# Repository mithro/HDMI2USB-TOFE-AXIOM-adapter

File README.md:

# TOFE to AXIOM Adapter

This repository contains a board for adapting the
[TOFE interface](https://tofe.io/) to the interface used by the
[plugin modules for the AXIOM Beta](https://wiki.apertus.org/index.php/AXIOM_Beta/AXIOM_Beta_Hardware#Plugin_Modules).

These adapter boards are **transparent** to the TOFE bus and have identical
schematics, only the PCB design differs.

Any **passive** PCI-Express adapter or riser which meets the PCI-Express
specification should be also compatible with the TOFE interface (but the
reverse is not necessarily true).

For more information on;
 * [The TOFE interface, see the HDMI2USB website](http://hdmi2usb.tv/tofe).
 * [The AXIOM interface, see the AXIOM wiki](https://wiki.apertus.org/index.php/AXIOM_Beta)
 * KiCad software, see [KiCad website](http://kicad.org/).

## Editing

Download with
```
git clone git+ssh://git@github.com/mithro/HDMI2USB-TOFE-AXIOM-Adapter.git --recursive
```

The designs in this repository was made using [KiCad](http://www.kicad.org/)
version **4.0.2 BZR 6225**
([the current stable version of KiCad](http://kicad.org/download/)).

## License

This work is copyright TimVideos.us Developers 2015 and licensed under a
Creative Commons Attribution-ShareAlike 4.0 International License.

You should have received a copy of the license along with this
work.  If not, see <http://creativecommons.org/licenses/by-sa/4.0/>.

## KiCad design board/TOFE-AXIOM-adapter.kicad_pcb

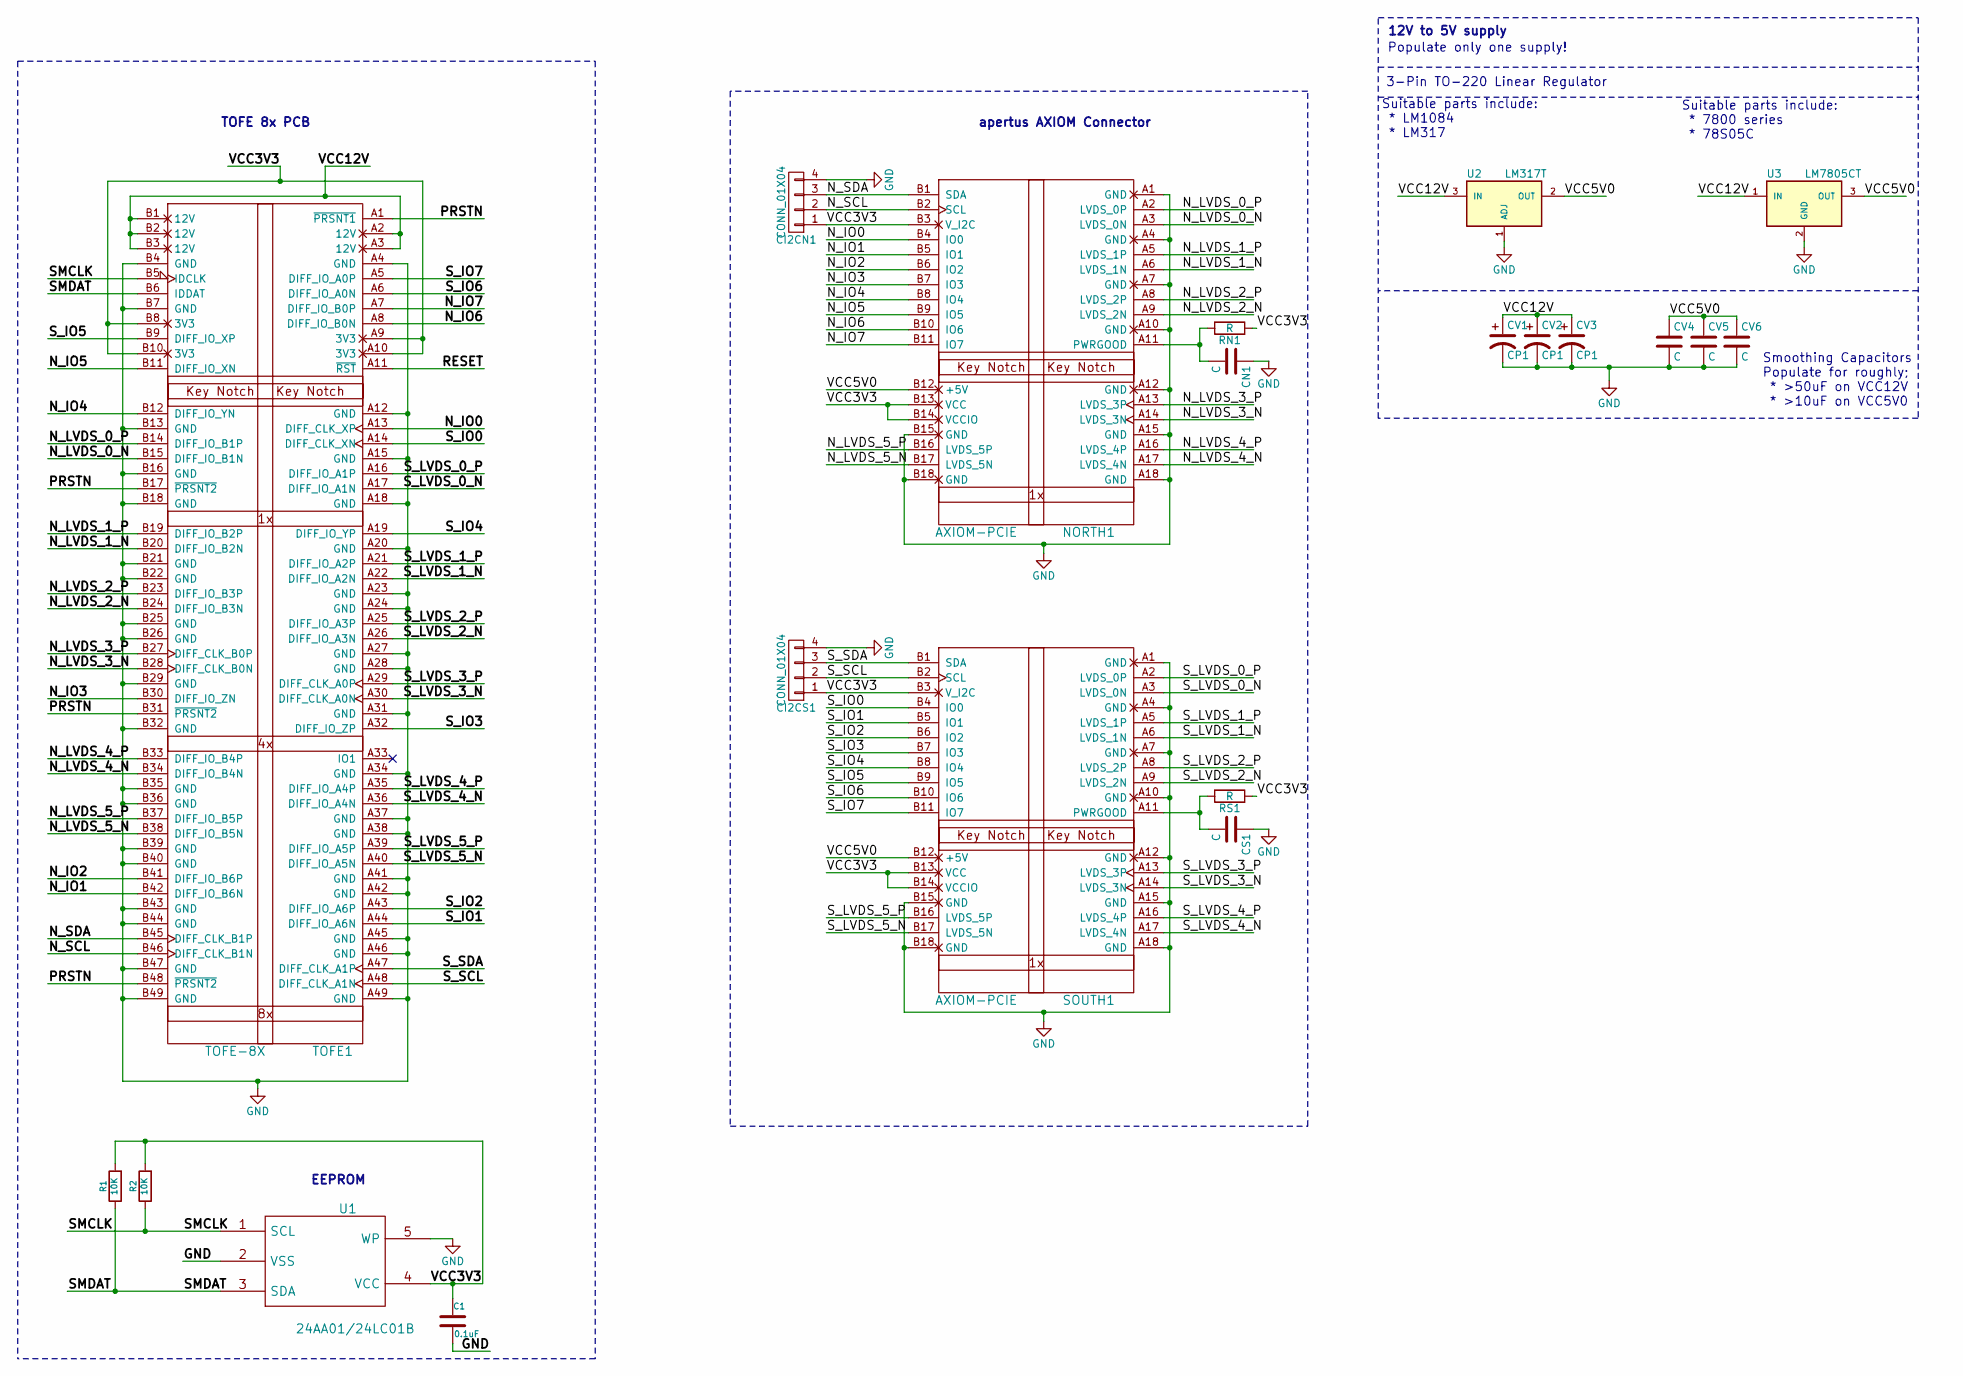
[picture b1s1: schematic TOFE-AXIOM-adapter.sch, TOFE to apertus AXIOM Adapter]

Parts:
C1: 0.1uF; C_1206_HandSoldering
CI2CN1, CI2CS1: CONN_01X04; Pin_Header_Straight_1x04
CN1: C; C_1206_HandSoldering
CS1: C; C_1206_HandSoldering
CV1, CV2, CV3: CP1; SMD-1206_Pol
CV4, CV5, CV6: C; C_1206_HandSoldering
NORTH1: AXIOM-PCIE; pci-x_conn-x1
R1, R2: 10K; R_0603_HandSoldering
RN1: R; R_0603_HandSoldering
RS1: R; R_0603_HandSoldering
SOUTH1: AXIOM-PCIE; pci-x_conn-x1
TOFE1: TOFE-8X; TOFE_8X_Pins
U1: 24AA01/24LC01B; SOT-23-5
U2: LM317T
U3: LM7805CT

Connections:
/N_IO0: NORTH1.B4 (IO0), TOFE1.A13 (DIFF_CLK_XP)
/N_IO1: NORTH1.B5 (IO1), TOFE1.B42 (DIFF_IO_B6N)
/N_IO2: NORTH1.B6 (IO2), TOFE1.B41 (DIFF_IO_B6P)
/N_IO3: NORTH1.B7 (IO3), TOFE1.B30 (DIFF_IO_ZN)
/N_IO4: NORTH1.B8 (IO4), TOFE1.B12 (DIFF_IO_YN)
/N_IO5: NORTH1.B9 (IO5), TOFE1.B11 (DIFF_IO_XN)
/N_IO6: NORTH1.B10 (IO6), TOFE1.A8 (DIFF_IO_B0N)
/N_IO7: NORTH1.B11 (IO7), TOFE1.A7 (DIFF_IO_B0P)
/N_LVDS_0_N: NORTH1.A3 (LVDS_0N), TOFE1.B15 (DIFF_IO_B1N)
/N_LVDS_0_P: NORTH1.A2 (LVDS_0P), TOFE1.B14 (DIFF_IO_B1P)
/N_LVDS_1_N: NORTH1.A6 (LVDS_1N), TOFE1.B20 (DIFF_IO_B2N)
/N_LVDS_1_P: NORTH1.A5 (LVDS_1P), TOFE1.B19 (DIFF_IO_B2P)
/N_LVDS_2_N: NORTH1.A9 (LVDS_2N), TOFE1.B24 (DIFF_IO_B3N)
/N_LVDS_2_P: NORTH1.A8 (LVDS_2P), TOFE1.B23 (DIFF_IO_B3P)
/N_LVDS_3_N: NORTH1.A14 (LVDS_3N), TOFE1.B28 (DIFF_CLK_B0N)
/N_LVDS_3_P: NORTH1.A13 (LVDS_3P), TOFE1.B27 (DIFF_CLK_B0P)
/N_LVDS_4_N: NORTH1.A17 (LVDS_4N), TOFE1.B34 (DIFF_IO_B4N)
/N_LVDS_4_P: NORTH1.A16 (LVDS_4P), TOFE1.B33 (DIFF_IO_B4P)
/N_LVDS_5_N: NORTH1.B17 (LVDS_5N), TOFE1.B38 (DIFF_IO_B5N)
/N_LVDS_5_P: NORTH1.B16 (LVDS_5P), TOFE1.B37 (DIFF_IO_B5P)
/N_SCL: CI2CN1.2, NORTH1.B2 (SCL), TOFE1.B46 (DIFF_CLK_B1N)
/N_SDA: CI2CN1.3, NORTH1.B1 (SDA), TOFE1.B45 (DIFF_CLK_B1P)
/PRSTN: TOFE1.A1 (~PRSNT1), TOFE1.B17 (~PRSNT2), TOFE1.B31 (~PRSNT2), TOFE1.B48 (~PRSNT2)
/RESET: TOFE1.A11 (~RST)
/SMCLK: R2.1, TOFE1.B5 (IDCLK), U1.1 (SCL)
/SMDAT: R1.1, TOFE1.B6 (IDDAT), U1.3 (SDA)
/S_IO0: SOUTH1.B4 (IO0), TOFE1.A14 (DIFF_CLK_XN)
/S_IO1: SOUTH1.B5 (IO1), TOFE1.A44 (DIFF_IO_A6N)
/S_IO2: SOUTH1.B6 (IO2), TOFE1.A43 (DIFF_IO_A6P)
/S_IO3: SOUTH1.B7 (IO3), TOFE1.A32 (DIFF_IO_ZP)
/S_IO4: SOUTH1.B8 (IO4), TOFE1.A19 (DIFF_IO_YP)
/S_IO5: SOUTH1.B9 (IO5), TOFE1.B9 (DIFF_IO_XP)
/S_IO6: SOUTH1.B10 (IO6), TOFE1.A6 (DIFF_IO_A0N)
/S_IO7: SOUTH1.B11 (IO7), TOFE1.A5 (DIFF_IO_A0P)
/S_LVDS_0_N: SOUTH1.A3 (LVDS_0N), TOFE1.A17 (DIFF_IO_A1N)
/S_LVDS_0_P: SOUTH1.A2 (LVDS_0P), TOFE1.A16 (DIFF_IO_A1P)
/S_LVDS_1_N: SOUTH1.A6 (LVDS_1N), TOFE1.A22 (DIFF_IO_A2N)
/S_LVDS_1_P: SOUTH1.A5 (LVDS_1P), TOFE1.A21 (DIFF_IO_A2P)
/S_LVDS_2_N: SOUTH1.A9 (LVDS_2N), TOFE1.A26 (DIFF_IO_A3N)
/S_LVDS_2_P: SOUTH1.A8 (LVDS_2P), TOFE1.A25 (DIFF_IO_A3P)
/S_LVDS_3_N: SOUTH1.A14 (LVDS_3N), TOFE1.A30 (DIFF_CLK_A0N)
/S_LVDS_3_P: SOUTH1.A13 (LVDS_3P), TOFE1.A29 (DIFF_CLK_A0P)
/S_LVDS_4_N: SOUTH1.A17 (LVDS_4N), TOFE1.A36 (DIFF_IO_A4N)
/S_LVDS_4_P: SOUTH1.A16 (LVDS_4P), TOFE1.A35 (DIFF_IO_A4P)
/S_LVDS_5_N: SOUTH1.B17 (LVDS_5N), TOFE1.A40 (DIFF_IO_A5N)
/S_LVDS_5_P: SOUTH1.B16 (LVDS_5P), TOFE1.A39 (DIFF_IO_A5P)
/S_SCL: CI2CS1.2, SOUTH1.B2 (SCL), TOFE1.A48 (DIFF_CLK_A1N)
/S_SDA: CI2CS1.3, SOUTH1.B1 (SDA), TOFE1.A47 (DIFF_CLK_A1P)
/VCC3V3: C1.1, CI2CN1.1, CI2CS1.1, NORTH1.B3 (V_I2C), NORTH1.B13 (VCC), NORTH1.B14 (VCCIO), R1.2, R2.2, RN1.1, RS1.1, SOUTH1.B3 (V_I2C), SOUTH1.B13 (VCC), SOUTH1.B14 (VCCIO), TOFE1.A9 (3V3), TOFE1.A10 (3V3), TOFE1.B8 (3V3), TOFE1.B10 (3V3), U1.4 (VCC)
/VCC5V0: CV4.1, CV5.1, CV6.1, NORTH1.B12 (+5V), SOUTH1.B12 (+5V), U2.2 (OUT), U3.3 (OUT)
/VCC12V: CV1.1, CV2.1, CV3.1, TOFE1.A2 (12V), TOFE1.A3 (12V), TOFE1.B1 (12V), TOFE1.B2 (12V), TOFE1.B3 (12V), U2.3 (IN), U3.1 (IN)
GND: C1.2, CI2CN1.4, CI2CS1.4, CN1.1, CS1.1, CV1.2, CV2.2, CV3.2, CV4.2, CV5.2, CV6.2, NORTH1.A1 (GND), NORTH1.A4 (GND), NORTH1.A7 (GND), NORTH1.A10 (GND), NORTH1.A12 (GND), NORTH1.A15 (GND), NORTH1.A18 (GND), NORTH1.B15 (GND), NORTH1.B18 (GND), SOUTH1.A1 (GND), SOUTH1.A4 (GND), SOUTH1.A7 (GND), SOUTH1.A10 (GND), SOUTH1.A12 (GND), SOUTH1.A15 (GND), SOUTH1.A18 (GND), SOUTH1.B15 (GND), SOUTH1.B18 (GND), TOFE1.A4 (GND), TOFE1.A12 (GND), TOFE1.A15 (GND), TOFE1.A18 (GND), TOFE1.A20 (GND), TOFE1.A23 (GND), TOFE1.A24 (GND), TOFE1.A27 (GND), TOFE1.A28 (GND), TOFE1.A31 (GND), TOFE1.A34 (GND), TOFE1.A37 (GND), TOFE1.A38 (GND), TOFE1.A41 (GND), TOFE1.A42 (GND), TOFE1.A45 (GND), TOFE1.A46 (GND), TOFE1.A49 (GND), TOFE1.B4 (GND), TOFE1.B7 (GND), TOFE1.B13 (GND), TOFE1.B16 (GND), TOFE1.B18 (GND), TOFE1.B21 (GND), TOFE1.B22 (GND), TOFE1.B25 (GND), TOFE1.B26 (GND), TOFE1.B29 (GND), TOFE1.B32 (GND), TOFE1.B35 (GND), TOFE1.B36 (GND), TOFE1.B39 (GND), TOFE1.B40 (GND), TOFE1.B43 (GND), TOFE1.B44 (GND), TOFE1.B47 (GND), TOFE1.B49 (GND), U1.2 (VSS), U1.5 (WP), U2.1 (ADJ), U3.2 (GND)
unnamed: CN1.2, NORTH1.A11 (PWRGOOD), RN1.2
unnamed: CS1.2, RS1.2, SOUTH1.A11 (PWRGOOD)

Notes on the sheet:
TOFE 8x PCB
apertus AXIOM Connector
EEPROM
12V to 5V supply
Populate only one supply!
3-Pin TO-220 Linear Regulator
Suitable parts include: * LM1084 * LM317
Suitable parts include: * 7800 series * 78S05C
Smoothing Capacitors Populate for roughly; * >50uF on VCC12V * >10uF on VCC5V0

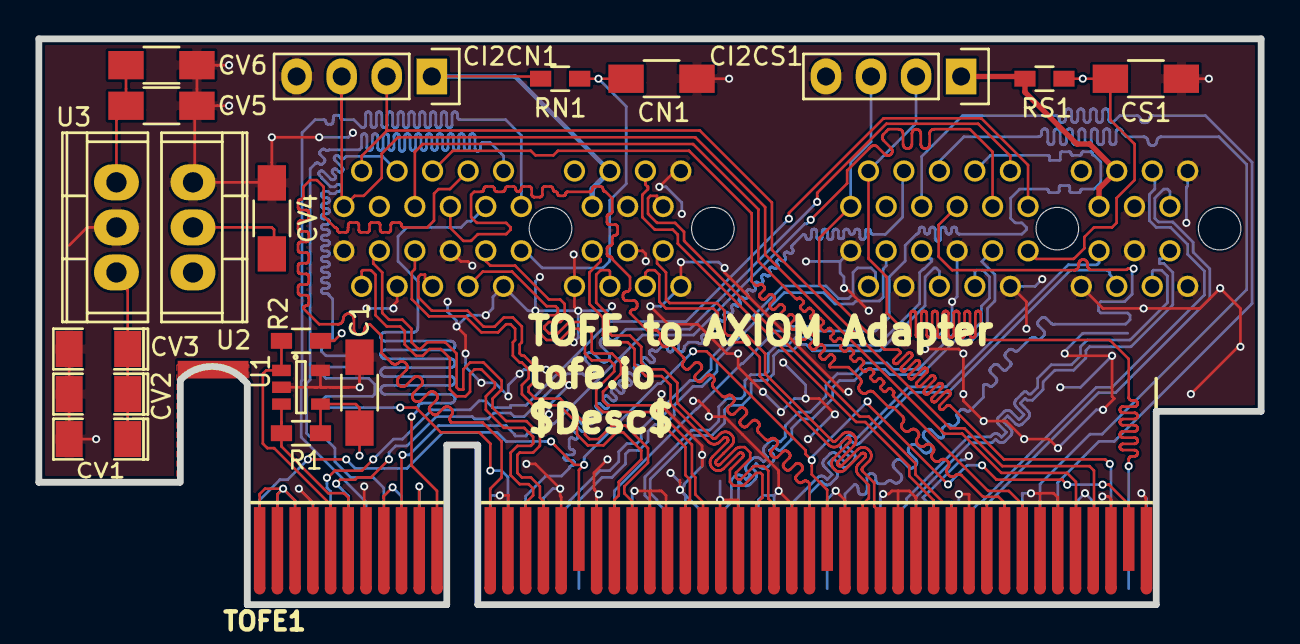
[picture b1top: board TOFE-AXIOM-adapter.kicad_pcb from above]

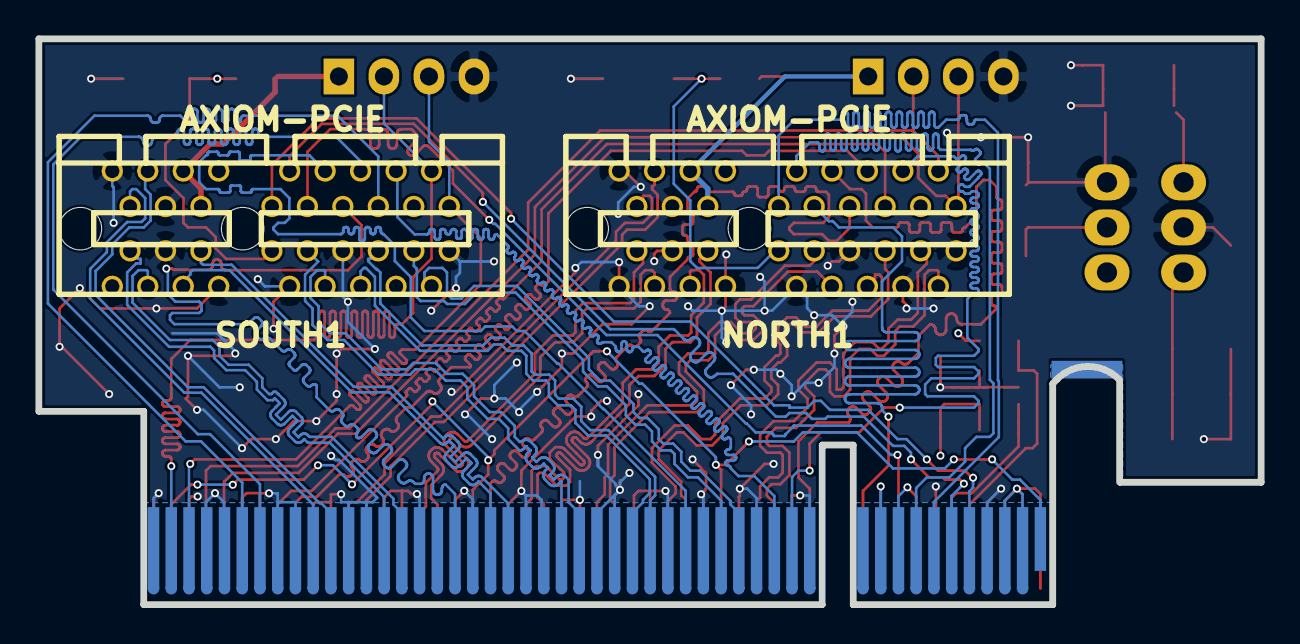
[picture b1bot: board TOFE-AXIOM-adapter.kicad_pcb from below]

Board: 4 copper layers, 68.9 x 31.9 mm, 21 parts (2 on the bottom side), 53 nets.

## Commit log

2016-03-18 Using the template as a library.
2016-03-18 Taking the TOFE left angle adapter as starting point.
    (Source from https://github.com/timvideos/HDMI2USB-TOFE-adapters-and-risers)
2016-03-18 Adding axiom part.
2016-03-18 Slowly working on the adapter.
2016-03-18 More work.
2016-03-18 Starting work on the PCB.
2016-03-18 Import PCI-Express connectors.
2016-03-18 Symlinking to the right place.
2016-03-18 Remove special library.
2016-03-18 Slowly getting there.
2016-03-18 Importing the ID EEPROM.
2016-03-18 Ignore backup files.
2016-03-18 Associating footprints.
2016-03-18 Fixing the diff pairs.
2016-03-18 Remove most of the routing from the PCB.
2016-03-18 Actually fixing the diff pairs.
2016-03-18 Slowly laying out the PCB.
2016-03-18 Routing.
2016-03-20 Working on routing.
2016-03-20 VCCIO set to 3V3
2016-03-20 Adding the DRC rules from the apertus group for their board.
2016-03-20 Changing wires to match DRC.
2016-03-20 Small fix.
2016-03-21 Moving the kicad submodule forward.
2016-03-21 Preparing for using "just the pins".
2016-03-21 Converted to just the pins footprint.
2016-03-21 Lots of fix ups.
2016-03-21 Adding a boundry trace to make the push/shove stuff easier to work with.
2016-03-21 Adding debug header for I2C lines.
2016-03-21 More routing.
2016-03-23 Adding 12V to 5V power supply.
2016-03-23 Adding annotations and parts.
2016-03-23 Adding more parts to the PCB.
2016-03-28 Fixed connector spacing to be 28.575 (rather then 28.500) spacing.
2016-03-28 Starting to get length matching checking working.
2016-03-28 Adding a check script.
2016-03-28 Fixing the length matching requirements.
2016-03-29 Updating the .gitmodules
2016-04-06 Added files via upload
2016-04-07 Updates from Dejan Stevanovic.
2016-04-07 Clean up of diff pairs.
2016-04-07 Length matching scripts updates.
2016-04-11 Low speed I/O" are matched to be roughly 10mil.
2016-05-23 Small cleanup.
2016-05-23 Making all the lengths actually match.
2016-05-28 Adding a .gitattributes file.
2016-05-28 Fixing via requirements.
2016-05-28 Fixing via sizes.
2016-05-28 Loading the fixed TOFE-8X Pins part.
2016-05-28 Fixing DRC caused by wrong via size usage.
2016-05-28 Fixing more DRC errors.
2016-05-28 Make VCC names consistent.
2016-05-28 Updating netlist.
2016-05-28 Using the inner layer for VCC routing.
2016-05-28 Updating netlist and adding VCC polygons.
2016-05-28 More fixing power supply.
2016-05-28 More power supply planes.
2016-05-28 More power fixes.
2016-05-28 More DRC fixing.
2016-06-01 Temp commit.
2016-06-14 Updating the README file.
2016-07-03 Removing interesting extra name.
2016-07-03 First drop from Phyllis.
2016-07-03 Fixing the EEPROM location in schematic.
2016-07-03 Updating submodule.
2016-07-03 Update for schematic changes.
2016-07-03 Setting VCCIO to VCC3V3.
2016-07-03 Fix pullup PWRGOOD circuit.
2016-07-08 Update number 3 from Phyllis.
2016-07-08 Adding fill zones on front / back.
2016-07-24 Update number 4 from Phyllis.
2016-08-01 Adding a release script.
2016-08-01 Adding output gerber directory.
2016-08-01 Creating gerbers v0.2-1-g36b3ea2 for TOFE-AXIOM-adapter
2016-08-01 Remove text on the back.
2016-08-03 Fix the release script.
2021-11-10 Update README.md
    https://forum.kicad.info/t/warning-avoid-all-links-to-kicad-pcb-org-use-kicad-org/31521

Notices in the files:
board/TOFE-AXIOM-adapter.kicad_pcb:
License : CC BY-SA
